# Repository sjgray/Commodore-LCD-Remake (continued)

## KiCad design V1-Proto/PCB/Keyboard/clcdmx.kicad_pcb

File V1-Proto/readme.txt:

CLCD Re-Make Project by Steve Gray and Mike Naberezny
==================== CBMSTEVE.CA

This folder contains the V1 prototype files.

The folders are:

3D             - STL files for 3D printed case and keycaps
CPLD           - Source for CPLD decode
Firmware       - Original and new firmware source and build scripts
CherryKeycaps  - SVG files to create custom cherry keycaps from MaxKeyboard.com
PCB            - Kicad design files for CLCD motherboard, EPROM-PLA, and MX Keyboard

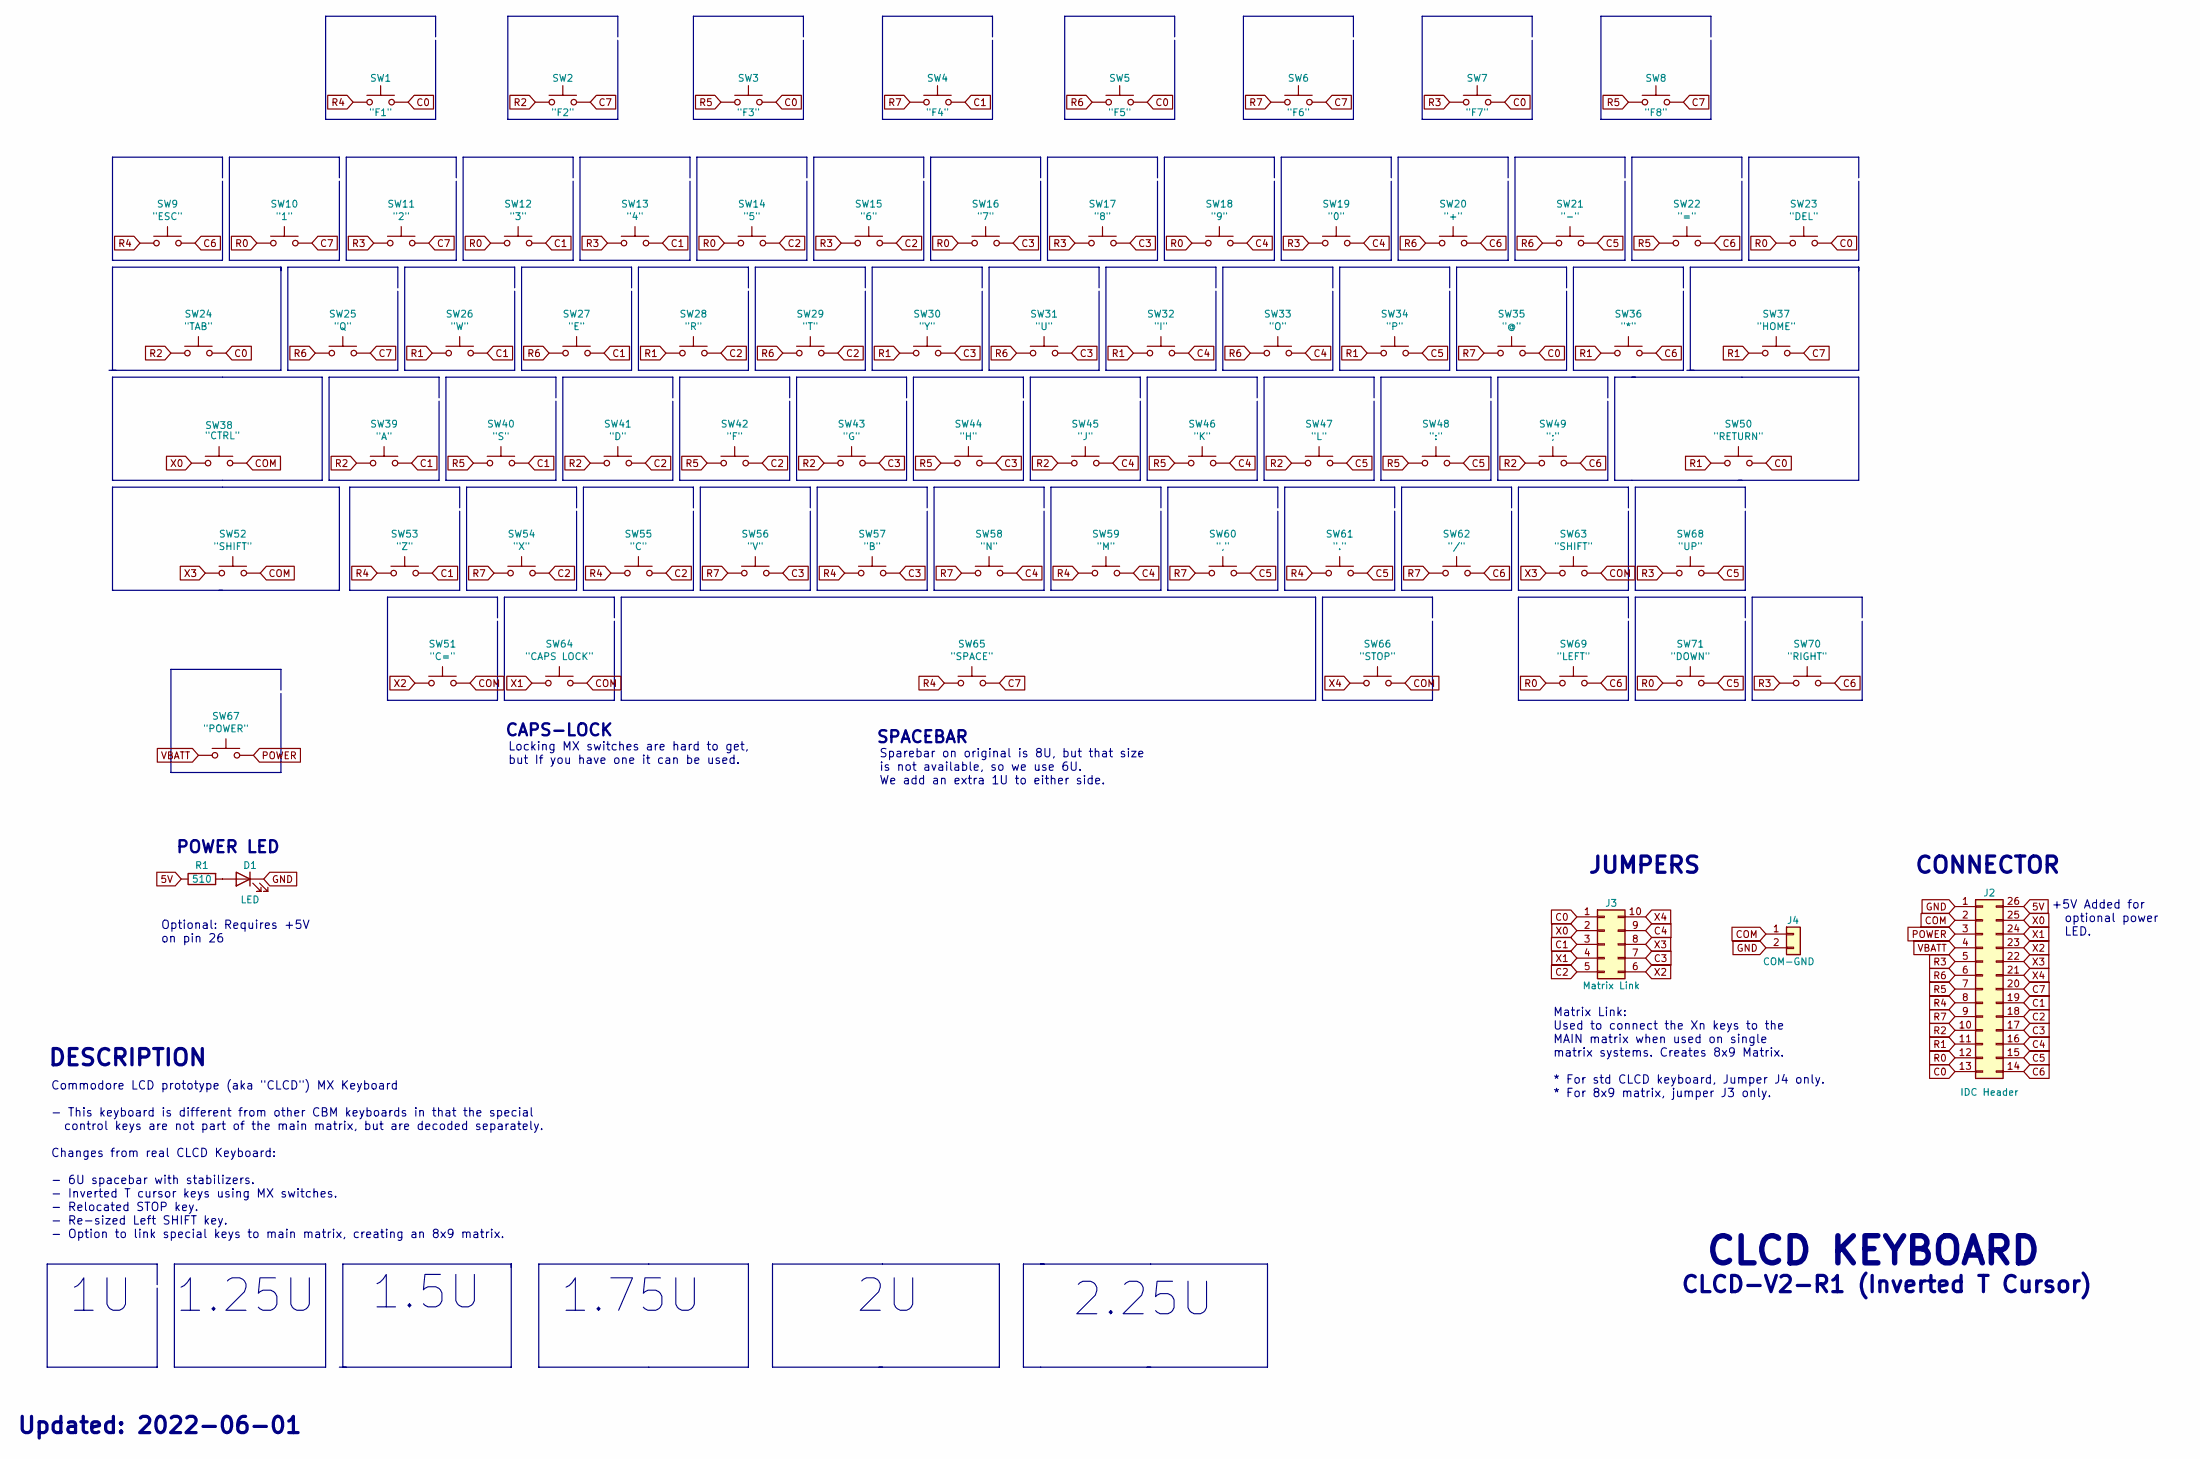
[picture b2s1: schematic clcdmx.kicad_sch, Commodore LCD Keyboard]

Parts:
D1: LED; PinHeader_2x01_P2.54mm_Vertical
J2: IDC Header; PinHeader_2x13_P2.54mm_Vertical
J3: Matrix Link; PinHeader_2x05_P2.54mm_Vertical
J4: COM-GND; PinHeader_1x02_P2.54mm_Vertical
R1: 510; R_Axial_DIN0204_L3.6mm_D1.6mm_P7.62mm_Horizontal
SW1: "F1"; SW_Cherry_MX_1.25u_PCB
SW2: "F2"; SW_Cherry_MX_1.25u_PCB
SW3: "F3"; SW_Cherry_MX_1.25u_PCB
SW4: "F4"; SW_Cherry_MX_1.25u_PCB
SW5: "F5"; SW_Cherry_MX_1.25u_PCB
SW6: "F6"; SW_Cherry_MX_1.25u_PCB
SW7: "F7"; SW_Cherry_MX_1.25u_PCB
SW8: "F8"; SW_Cherry_MX_1.25u_PCB
SW9: "ESC"; SW_Cherry_MX_1.00u_PCB
SW10: "1"; SW_Cherry_MX_1.00u_PCB
SW11: "2"; SW_Cherry_MX_1.00u_PCB
SW12: "3"; SW_Cherry_MX_1.00u_PCB
SW13: "4"; SW_Cherry_MX_1.00u_PCB
SW14: "5"; SW_Cherry_MX_1.00u_PCB
SW15: "6"; SW_Cherry_MX_1.00u_PCB
SW16: "7"; SW_Cherry_MX_1.00u_PCB
SW17: "8"; SW_Cherry_MX_1.00u_PCB
SW18: "9"; SW_Cherry_MX_1.00u_PCB
SW19: "0"; SW_Cherry_MX_1.00u_PCB
SW20: "+"; SW_Cherry_MX_1.00u_PCB
SW21: "-"; SW_Cherry_MX_1.00u_PCB
SW22: "="; SW_Cherry_MX_1.00u_PCB
SW23: "DEL"; SW_Cherry_MX_1.00u_PCB
SW24: "TAB"; SW_Cherry_MX_1.50u_PCB
SW25: "Q"; SW_Cherry_MX_1.00u_PCB
SW26: "W"; SW_Cherry_MX_1.00u_PCB
SW27: "E"; SW_Cherry_MX_1.00u_PCB
SW28: "R"; SW_Cherry_MX_1.00u_PCB
SW29: "T"; SW_Cherry_MX_1.00u_PCB
SW30: "Y"; SW_Cherry_MX_1.00u_PCB
SW31: "U"; SW_Cherry_MX_1.00u_PCB
SW32: "I"; SW_Cherry_MX_1.00u_PCB
SW33: "O"; SW_Cherry_MX_1.00u_PCB
SW34: "P"; SW_Cherry_MX_1.00u_PCB
SW35: "@"; SW_Cherry_MX_1.00u_PCB
SW36: "*"; SW_Cherry_MX_1.00u_PCB
SW37: "HOME"; SW_Cherry_MX_1.50u_PCB
SW38: "CTRL"; SW_Cherry_MX_1.75u_PCB
SW39: "A"; SW_Cherry_MX_1.00u_PCB
SW40: "S"; SW_Cherry_MX_1.00u_PCB
SW41: "D"; SW_Cherry_MX_1.00u_PCB
SW42: "F"; SW_Cherry_MX_1.00u_PCB
SW43: "G"; SW_Cherry_MX_1.00u_PCB
SW44: "H"; SW_Cherry_MX_1.00u_PCB
SW45: "J"; SW_Cherry_MX_1.00u_PCB
SW46: "K"; SW_Cherry_MX_1.00u_PCB
SW47: "L"; SW_Cherry_MX_1.00u_PCB
SW48: ":"; SW_Cherry_MX_1.00u_PCB
SW49: ";"; SW_Cherry_MX_1.00u_PCB
SW50: "RETURN"; SW_Cherry_MX_2.25u_PCB
SW51: "C="; SW_Cherry_MX_1.00u_PCB
SW52: "SHIFT"; SW_Cherry_MX_2.00u_PCB
SW53: "Z"; SW_Cherry_MX_1.00u_PCB
SW54: "X"; SW_Cherry_MX_1.00u_PCB
SW55: "C"; SW_Cherry_MX_1.00u_PCB
SW56: "V"; SW_Cherry_MX_1.00u_PCB
SW57: "B"; SW_Cherry_MX_1.00u_PCB
SW58: "N"; SW_Cherry_MX_1.00u_PCB
SW59: "M"; SW_Cherry_MX_1.00u_PCB
SW60: ","; SW_Cherry_MX_1.00u_PCB
SW61: "."; SW_Cherry_MX_1.00u_PCB
SW62: "/"; SW_Cherry_MX_1.00u_PCB
SW63: "SHIFT"; SW_Cherry_MX_1.00u_PCB
SW64: "CAPS LOCK"; SW_Cherry_MX_1.00u_PCB
SW65: "SPACE"; SW_Cherry_MX_6.0u_PCB
SW66: "STOP"; SW_Cherry_MX_1.00u_PCB
SW67: "POWER"; SW_Cherry_MX_1.00u_PCB
SW68: "UP"; SW_Cherry_MX_1.00u_PCB
SW69: "LEFT"; SW_Cherry_MX_1.00u_PCB
SW70: "RIGHT"; SW_Cherry_MX_1.00u_PCB
SW71: "DOWN"; SW_Cherry_MX_1.00u_PCB

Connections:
5V: J2.26, R1.1
C0: J2.13, J3.1, SW1.2, SW3.2, SW5.2, SW7.2, SW23.2, SW24.2, SW35.2, SW50.2
C1: J2.19, J3.3, SW4.2, SW12.2, SW13.2, SW26.2, SW27.2, SW39.2, SW40.2, SW53.2
C2: J2.18, J3.5, SW14.2, SW15.2, SW28.2, SW29.2, SW41.2, SW42.2, SW54.2, SW55.2
C3: J2.17, J3.7, SW16.2, SW17.2, SW30.2, SW31.2, SW43.2, SW44.2, SW56.2, SW57.2
C4: J2.16, J3.9, SW18.2, SW19.2, SW32.2, SW33.2, SW45.2, SW46.2, SW58.2, SW59.2
C5: J2.15, SW21.2, SW34.2, SW47.2, SW48.2, SW60.2, SW61.2, SW68.2, SW71.2
C6: J2.14, SW9.2, SW20.2, SW22.2, SW36.2, SW49.2, SW62.2, SW69.2, SW70.2
C7: J2.20, SW2.2, SW6.2, SW8.2, SW10.2, SW11.2, SW25.2, SW37.2, SW65.2
COM: J2.2, J4.1, SW38.2, SW51.2, SW52.2, SW63.2, SW64.2, SW66.2
GND: D1.1 (K), J2.1, J4.2
unnamed: D1.2 (A), R1.2
POWER: J2.3, SW67.2
R0: J2.12, SW10.1, SW12.1, SW14.1, SW16.1, SW18.1, SW23.1, SW69.1, SW71.1
R1: J2.11, SW26.1, SW28.1, SW30.1, SW32.1, SW34.1, SW36.1, SW37.1, SW50.1
R2: J2.10, SW2.1, SW24.1, SW39.1, SW41.1, SW43.1, SW45.1, SW47.1, SW49.1
R3: J2.5, SW7.1, SW11.1, SW13.1, SW15.1, SW17.1, SW19.1, SW68.1, SW70.1
R4: J2.8, SW1.1, SW9.1, SW53.1, SW55.1, SW57.1, SW59.1, SW61.1, SW65.1
R5: J2.7, SW3.1, SW8.1, SW22.1, SW40.1, SW42.1, SW44.1, SW46.1, SW48.1
R6: J2.6, SW5.1, SW20.1, SW21.1, SW25.1, SW27.1, SW29.1, SW31.1, SW33.1
R7: J2.9, SW4.1, SW6.1, SW35.1, SW54.1, SW56.1, SW58.1, SW60.1, SW62.1
VBATT: J2.4, SW67.1
X0: J2.25, J3.2, SW38.1
X1: J2.24, J3.4, SW64.1
X2: J2.23, J3.6, SW51.1
X3: J2.22, J3.8, SW52.1, SW63.1
X4: J2.21, J3.10, SW66.1

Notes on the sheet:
Locking MX switches are hard to get, but If you have one it can be used.
Sparebar on original is 8U, but that size is not available, so we use 6U. We add an extra 1U to either side.
1.75U
Optional: Requires +5V on pin 26
2.25U
POWER LED
1.5U
Matrix Link: Used to connect the Xn keys to the MAIN matrix when used on single matrix systems. Creates 8x9 Matrix. * For std CLCD keyboard, Jumper J4 only. * For 8x9 matrix, jumper J3 only.
Commodore LCD prototype (aka "CLCD") MX Keyboard - This keyboard is different from other CBM keyboards in that the special control keys are not part of the main matrix, but are decoded separately. Changes from real CLCD Keyboard: - 6U spacebar with stabilizers. - Inverted T cursor keys using MX swi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
CONNECTOR
CLCD-V2-R1 (Inverted T Cursor)
1.25U
CAPS-LOCK
JUMPERS
+5V Added for optional power LED.
SPACEBAR
DESCRIPTION
Updated: 2022-06-01
CLCD KEYBOARD

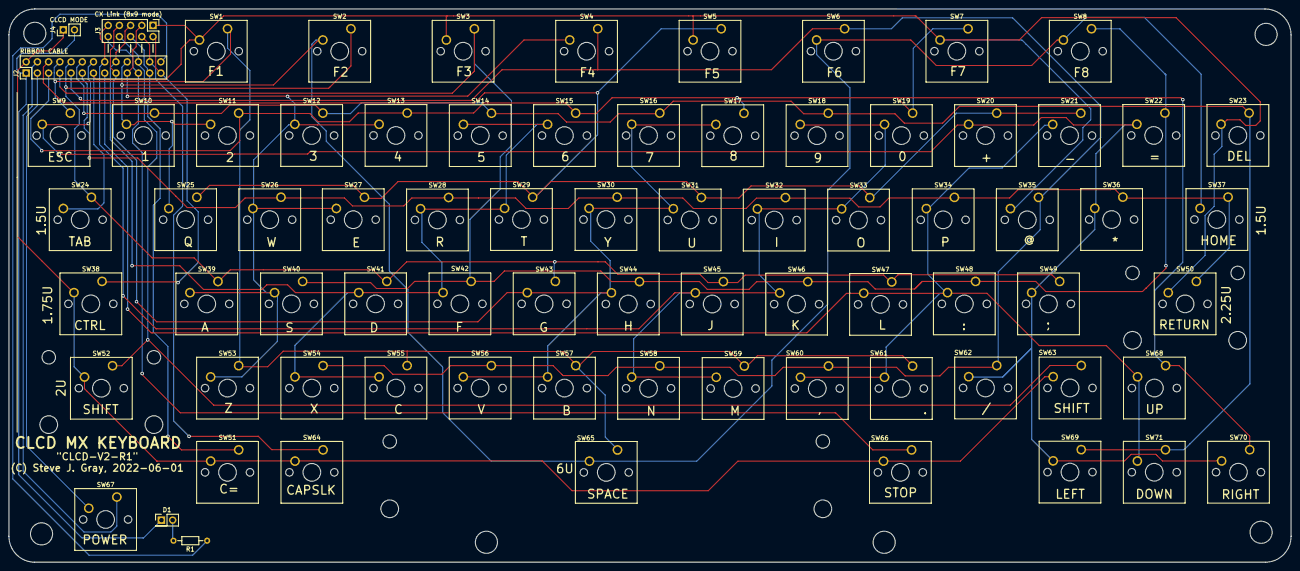
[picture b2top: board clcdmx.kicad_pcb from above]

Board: 2 copper layers, 290.1 x 125.2 mm, 76 parts (0 on the bottom side), 27 nets.

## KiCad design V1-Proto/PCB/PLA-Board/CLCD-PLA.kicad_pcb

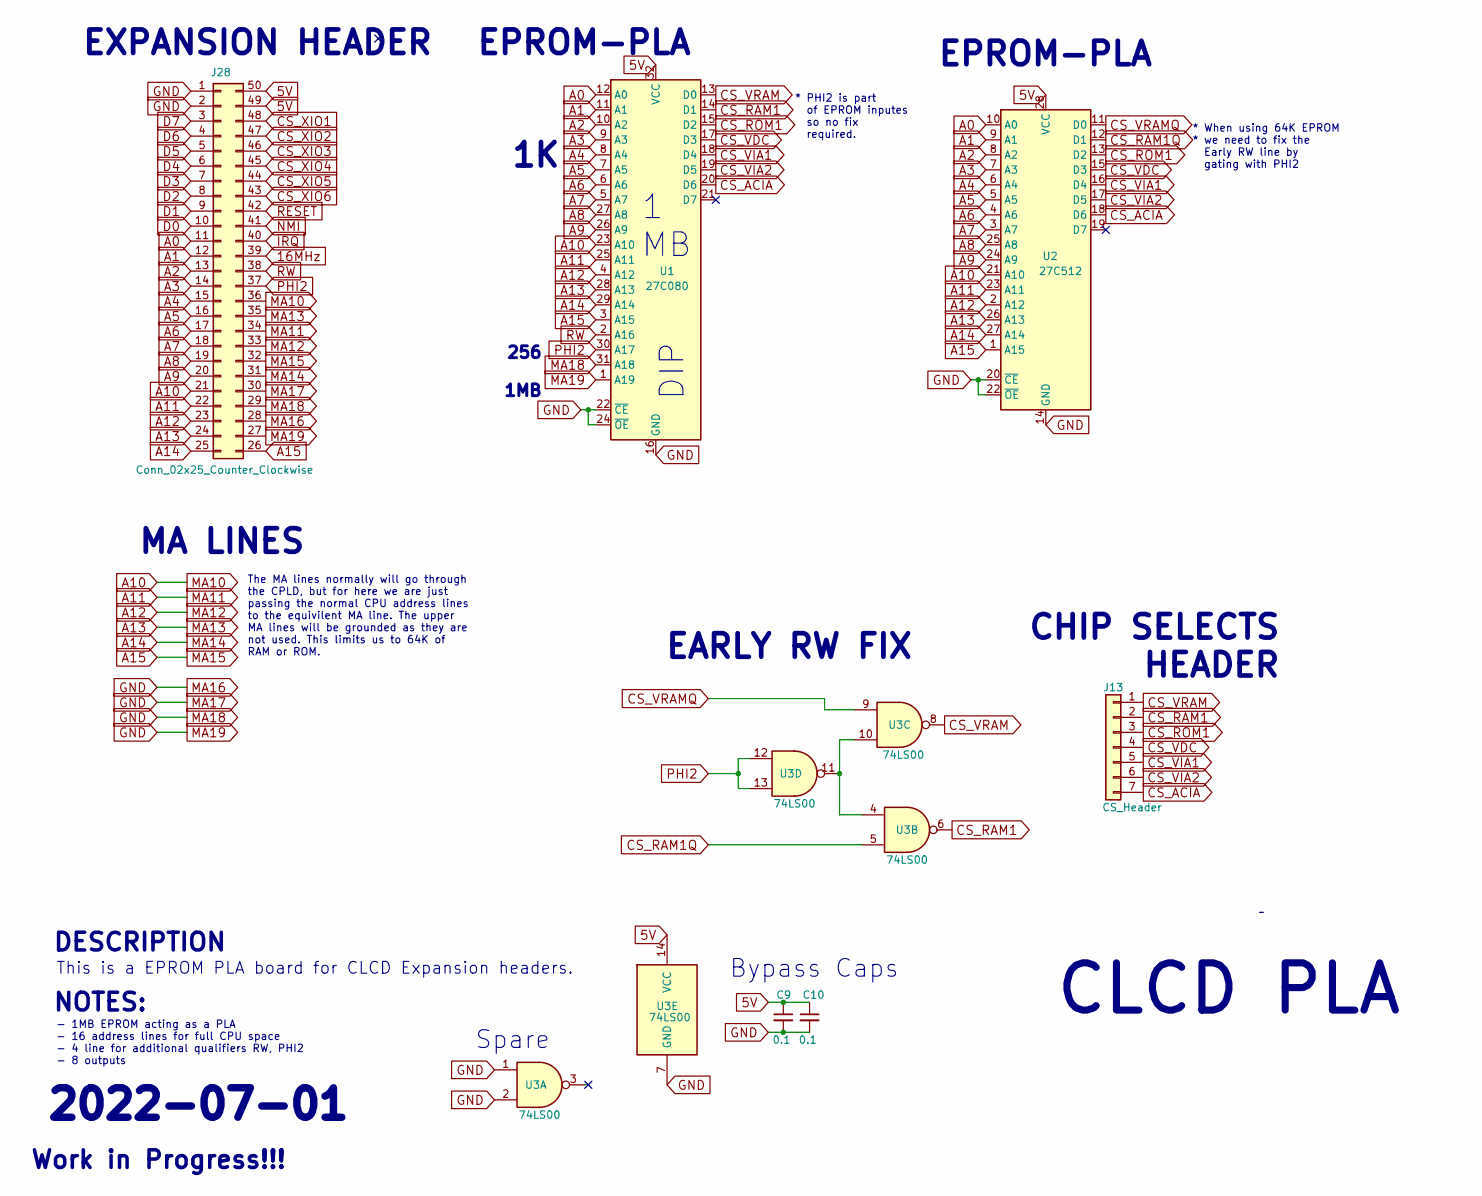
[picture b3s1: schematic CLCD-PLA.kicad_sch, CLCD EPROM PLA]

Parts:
C9, C10: 0.1; C_Disc_D4.7mm_W2.5mm_P5.00mm
J13: CS_Header; PinHeader_1x07_P2.54mm_Vertical
J28: Conn_02x25_Counter_Clockwise; PinHeader_2x25_P2.54mm_Vertical
U1: 27C080; DIP-32_W15.24mm_LongPads
U2: 27C512; DIP-28_W15.24mm
U3: 74LS00; DIP-14_W7.62mm_LongPads

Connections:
5V: C9.1, C10.1, J28.49, J28.50, U1.32 (VCC), U2.28 (VCC), U3.14 (VCC)
16MHz: J28.39
A0: J28.11, U1.12 (A0), U2.10 (A0)
A1: J28.12, U1.11 (A1), U2.9 (A1)
A2: J28.13, U1.10 (A2), U2.8 (A2)
A3: J28.14, U1.9 (A3), U2.7 (A3)
A4: J28.15, U1.8 (A4), U2.6 (A4)
A5: J28.16, U1.7 (A5), U2.5 (A5)
A6: J28.17, U1.6 (A6), U2.4 (A6)
A7: J28.18, U1.5 (A7), U2.3 (A7)
A8: J28.19, U1.27 (A8), U2.25 (A8)
A9: J28.20, U1.26 (A9), U2.24 (A9)
A10: J28.21, J28.36, U1.23 (A10), U2.21 (A10)
A11: J28.22, J28.34, U1.25 (A11), U2.23 (A11)
A12: J28.23, J28.33, U1.4 (A12), U2.2 (A12)
A13: J28.24, J28.35, U1.28 (A13), U2.26 (A13)
A14: J28.25, J28.31, U1.29 (A14), U2.27 (A14)
A15: J28.26, J28.32, U1.3 (A15), U2.1 (A15)
CS_ACIA: J13.7, U1.20 (D6), U2.18 (D6)
CS_RAM1: J13.2, U1.14 (D1), U3.6
CS_RAM1Q: U2.12 (D1), U3.5
CS_ROM1: J13.3, U1.15 (D2), U2.13 (D2)
CS_VDC: J13.4, U1.17 (D3), U2.15 (D3)
CS_VIA1: J13.5, U1.18 (D4), U2.16 (D4)
CS_VIA2: J13.6, U1.19 (D5), U2.17 (D5)
CS_VRAM: J13.1, U1.13 (D0), U3.8
CS_VRAMQ: U2.11 (D0), U3.9
CS_XIO1: J28.48
CS_XIO2: J28.47
CS_XIO3: J28.46
CS_XIO4: J28.45
CS_XIO5: J28.44
CS_XIO6: J28.43
D0: J28.10
D1: J28.9
D2: J28.8
D3: J28.7
D4: J28.6
D5: J28.5
D6: J28.4
D7: J28.3
GND: C9.2, C10.2, J28.1, J28.2, J28.27, J28.28, J28.29, J28.30, U1.1 (A19), U1.16 (GND), U1.22 (~CE), U1.24 (~OE), U1.31 (A18), U2.14 (GND), U2.20 (~CE), U2.22 (~OE), U3.1, U3.2, U3.7 (GND)
unnamed: U3.4, U3.10, U3.11
PHI2: J28.37, U1.30 (A17), U3.12, U3.13
RESET: J28.42
RW: J28.38, U1.2 (A16)
~IRQ: J28.40
~NMI: J28.41

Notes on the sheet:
DESCRIPTION
CHIP SELECTS HEADER
EPROM-PLA
Work in Progress!!!
The MA lines normally will go through the CPLD, but for here we are just passing the normal CPU address lines to the equivilent MA line. The upper MA lines will be grounded as they are not used. This limits us to 64K of RAM or ROM.
NOTES:
This is a EPROM PLA board for CLCD Expansion headers.
Spare
Bypass Caps
2022-07-01
EARLY RW FIX
* When using 64K EPROM * we need to fix the Early RW line by gating with PHI2
1 MB
MA LINES
* PHI2 is part of EPROM inputes so no fix required.
CLCD PLA
256 1MB
- 1MB EPROM acting as a PLA - 16 address lines for full CPU space - 4 line for additional qualifiers RW, PHI2 - 8 outputs
DIP
EXPANSION HEADER

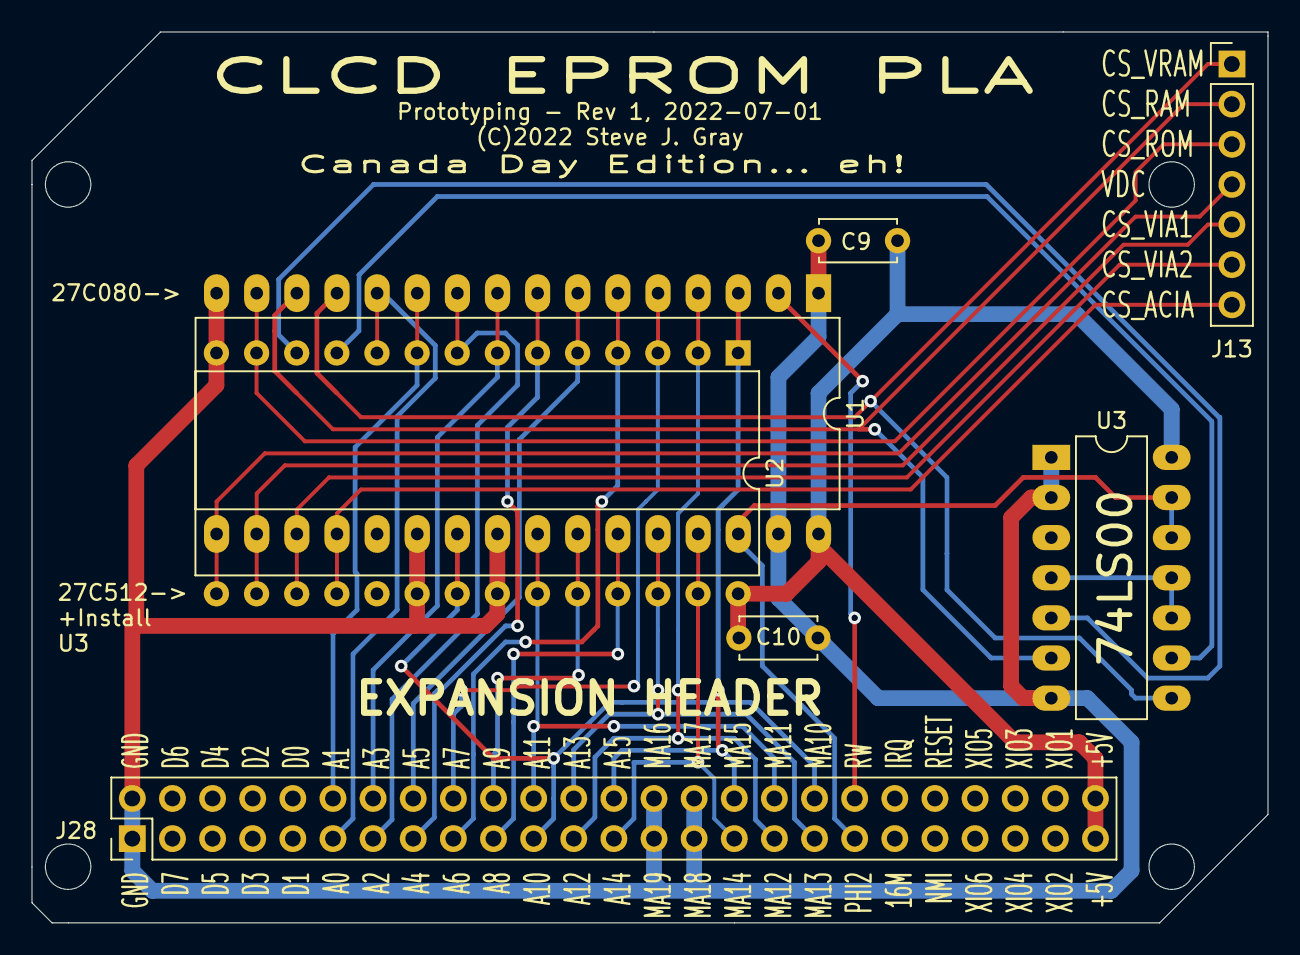
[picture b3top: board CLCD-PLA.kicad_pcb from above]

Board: 2 copper layers, 78.2 x 56.4 mm, 7 parts (0 on the bottom side), 30 nets.

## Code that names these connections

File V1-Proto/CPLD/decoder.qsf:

# -------------------------------------------------------------------------- #
#
# Copyright (C) 1991-2013 Altera Corporation
# Your use of Altera Corporation's design tools, logic functions 
# and other software and tools, and its AMPP partner logic 
# functions, and any output files from any of the foregoing 
# (including device programming or simulation files), and any 
# associated documentation or information are expressly subject 
# to the terms and conditions of the Altera Program License 
# Subscription Agreement, Altera MegaCore Function License 
# Agreement, or other applicable license agreement, including, 
# without limitation, that your use is for the sole purpose of 
# programming logic devices manufactured by Altera and sold by 
# Altera or its authorized distributors.  Please refer to the 
# applicable agreement for further details.
#
# -------------------------------------------------------------------------- #
#
# Quartus II 64-Bit
# Version 13.0.1 Build 232 06/12/2013 Service Pack 1 SJ Web Edition
# Date created = 16:04:12  January 04, 2023
#
# -------------------------------------------------------------------------- #
#
# Notes:
#
# 1) The default values for assignments are stored in the file:
#		decoder_assignment_defaults.qdf
#    If this file doesn't exist, see file:
#		assignment_defaults.qdf
#
# 2) Altera recommends that you do not modify this file. This
#    file is updated automatically by the Quartus II software
#    and any changes you make may be lost or overwritten.
#
# -------------------------------------------------------------------------- #


set_global_assignment -name FAMILY MAX7000S
set_global_assignment -name DEVICE "EPM7128SLC84-15"
set_global_assignment -name TOP_LEVEL_ENTITY decoder
set_global_assignment -name ORIGINAL_QUARTUS_VERSION "13.0 SP1"
set_global_assignment -name PROJECT_CREATION_TIME_DATE "16:04:12  JANUARY 04, 2023"
set_global_assignment -name LAST_QUARTUS_VERSION "13.0 SP1"
set_global_assignment -name PROJECT_OUTPUT_DIRECTORY output_files
set_global_assignment -name ERROR_CHECK_FREQUENCY_DIVISOR "-1"
set_global_assignment -name EDA_SIMULATION_TOOL "ModelSim-Altera (VHDL)"
set_global_assignment -name EDA_OUTPUT_DATA_FORMAT VHDL -section_id eda_simulation
set_global_assignment -name MAX7000_DEVICE_IO_STANDARD TTL
set_location_assignment PIN_2 -to phi2
set_location_assignment PIN_1 -to resetb
set_location_assignment PIN_83 -to osc
set_location_assignment PIN_4 -to cs_vramb
set_location_assignment PIN_5 -to cs_ram1b
set_location_assignment PIN_6 -to cs_rom1b
set_location_assignment PIN_8 -to cs_vdcb
set_location_assignment PIN_9 -to cs_via1b
set_location_assignment PIN_10 -to cs_via2b
set_location_assignment PIN_12 -to cpu_clk
set_location_assignment PIN_15 -to vdc_dclk
set_location_assignment PIN_17 -to vdc_fontopt
set_location_assignment PIN_16 -to vdc_romram
set_location_assignment PIN_73 -to d[0]
set_location_assignment PIN_74 -to d[1]
set_location_assignment PIN_75 -to d[2]
set_location_assignment PIN_76 -to d[3]
set_location_assignment PIN_77 -to d[4]
set_location_assignment PIN_79 -to d[5]
set_location_assignment PIN_80 -to d[6]
set_location_assignment PIN_81 -to d[7]
set_location_assignment PIN_30 -to ma[10]
set_location_assignment PIN_28 -to ma[11]
set_location_assignment PIN_27 -to ma[12]
set_location_assignment PIN_29 -to ma[13]
set_location_assignment PIN_24 -to ma[14]
set_location_assignment PIN_25 -to ma[15]
set_location_assignment PIN_20 -to ma[16]
set_location_assignment PIN_22 -to ma[17]
set_location_assignment PIN_21 -to ma[18]
set_location_assignment PIN_18 -to ma[19]
set_location_assignment PIN_51 -to a[0]
set_location_assignment PIN_52 -to a[1]
set_location_assignment PIN_54 -to a[2]
set_location_assignment PIN_55 -to a[3]
set_location_assignment PIN_56 -to a[4]
set_location_assignment PIN_57 -to a[5]
set_location_assignment PIN_58 -to a[6]
set_location_assignment PIN_60 -to a[7]
set_location_assignment PIN_61 -to a[8]
set_location_assignment PIN_63 -to a[9]
set_location_assignment PIN_64 -to a[10]
set_location_assignment PIN_65 -to a[11]
set_location_assignment PIN_67 -to a[12]
set_location_assignment PIN_68 -to a[13]
set_location_assignment PIN_69 -to a[14]
set_location_assignment PIN_70 -to a[15]
set_location_assignment PIN_39 -to j2[0]
set_location_assignment PIN_40 -to j2[1]
set_location_assignment PIN_41 -to j2[2]
set_location_assignment PIN_44 -to j2[3]
set_location_assignment PIN_45 -to j2[4]
set_location_assignment PIN_46 -to j2[5]
set_location_assignment PIN_48 -to j2[6]
set_location_assignment PIN_49 -to j2[7]
set_location_assignment PIN_50 -to rwb
set_location_assignment PIN_11 -to cs_aciab
set_global_assignment -name OPTIMIZE_HOLD_TIMING OFF
set_global_assignment -name OPTIMIZE_MULTI_CORNER_TIMING OFF
set_global_assignment -name FITTER_EFFORT "STANDARD FIT"
set_global_assignment -name SDC_FILE decoder.sdc
set_global_assignment -name VHDL_FILE decoder_testbench.vhd
set_global_assignment -name VHDL_FILE decoder.vhd -hdl_version VHDL_2008
set_global_assignment -name CDF_FILE ../output_files/Chain5.cdf

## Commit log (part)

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2025-12-20 My Commodore LCD Re-creation Project
    Initial release - Complete V1 project files. V2 work-in-progress PCB.
2025-12-22 Add some pics of V1
    Add some pics of pcb development, case and design, keyboard, etc.
2025-12-27 start of the MMU implementation
2025-12-27 fixed indentation
2025-12-27 new testbench
2025-12-27 fix testbench, new readme, and new timing constraints
2025-12-27 reset all registers on reset
2025-12-27 change VDC base from to
2025-12-27 generate chip select based on physical address and MMU mode
2025-12-28 Add Sketchup files
    Add Sketchup files for Case in folder. Moved STL files to folder. Update Readme.
